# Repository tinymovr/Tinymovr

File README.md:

[Tinymovr is an affordable motor controller](https://tinymovr.com) with integrated encoder and CAN bus for precise control of 3-phase brushless motors (PMSMs). 

This repository holds the open source firmware, client library, hardware designs and documentation source.

> **Note**
>
> This is the latest stable version of the Tinymovr Firmware and Studio app. For the legacy 0.x.x version, check out the [legacy branch](https://github.com/tinymovr/Tinymovr/tree/attic/legacy).

## Getting Started

Please visit the [Quick Start Guide](https://tinymovr.readthedocs.io/en/latest/quickstart.html)

## Getting Help

[Full documentation is available at Readthedocs](https://tinymovr.readthedocs.io).

Please visit the [Discussions Page](https://github.com/tinymovr/Tinymovr/discussions) and the [Discord Server](https://discord.gg/vNvmpfthug) to ask any questions. If you are unable to find an answer to your question, you are welcome to [start a new discussion](https://github.com/tinymovr/Tinymovr/discussions/new/choose) or ask away at [our Discord server](https://discord.gg/vNvmpfthug).

If you would like to propose a feature or think you have found a bug, [open a new issue](https://github.com/tinymovr/Tinymovr/issues/new).

### Repository Structure

> **Note**: The `main` branch reflects the latest release. Development happens on [develop](https://github.com/tinymovr/Tinymovr/tree/develop).

The repository is organized as follows:

[firmware](./firmware/): Firmware for the PAC5527 MCU in Tinymovr

[studio](./studio/): Tinymovr Studio client software and library

[hardware](./hardware): Designs and drawings for related hardware

[docs](./docs): User documentation source (built with Sphinx)

See also: Developer documentation in root (ARCHITECTURE.md, CONTRIBUTING.md, etc.)

### Developer Documentation

For contributors and AI agents working with the codebase:

- **[ARCHITECTURE.md](ARCHITECTURE.md)** - System design and module organization
- **[CONTRIBUTING.md](CONTRIBUTING.md)** - Setup, workflow, and PR process
- **[SAFETY.md](SAFETY.md)** - Safety-critical constraints (read before modifying firmware)
- **[CLAUDE.md](CLAUDE.md)** - Navigation guide for AI agents

Additional technical documentation:
- [AVLOS_GUIDE.md](AVLOS_GUIDE.md) - Protocol modification workflow
- [CONVENTIONS.md](CONVENTIONS.md) - Code style and patterns
- [TESTING.md](TESTING.md) - Testing practices
- [STRUCTURE.md](STRUCTURE.md) - Directory organization
- [PAC5527_NOTES.md](PAC5527_NOTES.md) - MCU architecture

## Versioning

We use [SemVer](http://semver.org/) for versioning. For the versions available, see the [tags on this repository](https://github.com/tinymovr/tinymovr/tags). 

## Contributing

Pull requests are welcome. For major changes, please open an issue first to discuss what you would like to change.

**New contributors**: See [CONTRIBUTING.md](CONTRIBUTING.md) for setup instructions and workflow.

**AI agents**: See [CLAUDE.md](CLAUDE.md) for navigation and guidelines.

## License

[GPLv3](https://choosealicense.com/licenses/gpl-3.0/)

### External Links

[Tinymovr Website and Store](https://tinymovr.com)

[Blog](https://tinymovr.com/blogs/news)

[Discord server](https://discord.gg/vNvmpfthug)

[Project page on Hackaday](https://hackaday.io/project/168650-tinymovr-motor-controller)

[BLDC-Design-Help Repository](https://github.com/ThotAlion/BLDC-design-help), with lots of useful information and Tinymovr benchmarks

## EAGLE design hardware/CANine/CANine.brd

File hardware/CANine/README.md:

# CANine CAN Adapter

This is a USB Type-C <-> CAN Bus adapter. Itself it is an adaptation of the [CANable board](https://canable.io/). It features DF-13 connectors in addition to 2.54mm header, as well as a convenient DIP switch for setting CAN termination resistor and boot mode.

This design is released under the original CANable license.

This directory also includes an STL model for a 3D printable case for the adapter.

There is also an [alternative case design available](https://github.com/ThotAlion/BLDC-design-help/tree/main/STL/USBCANBox) by ThotAlion.

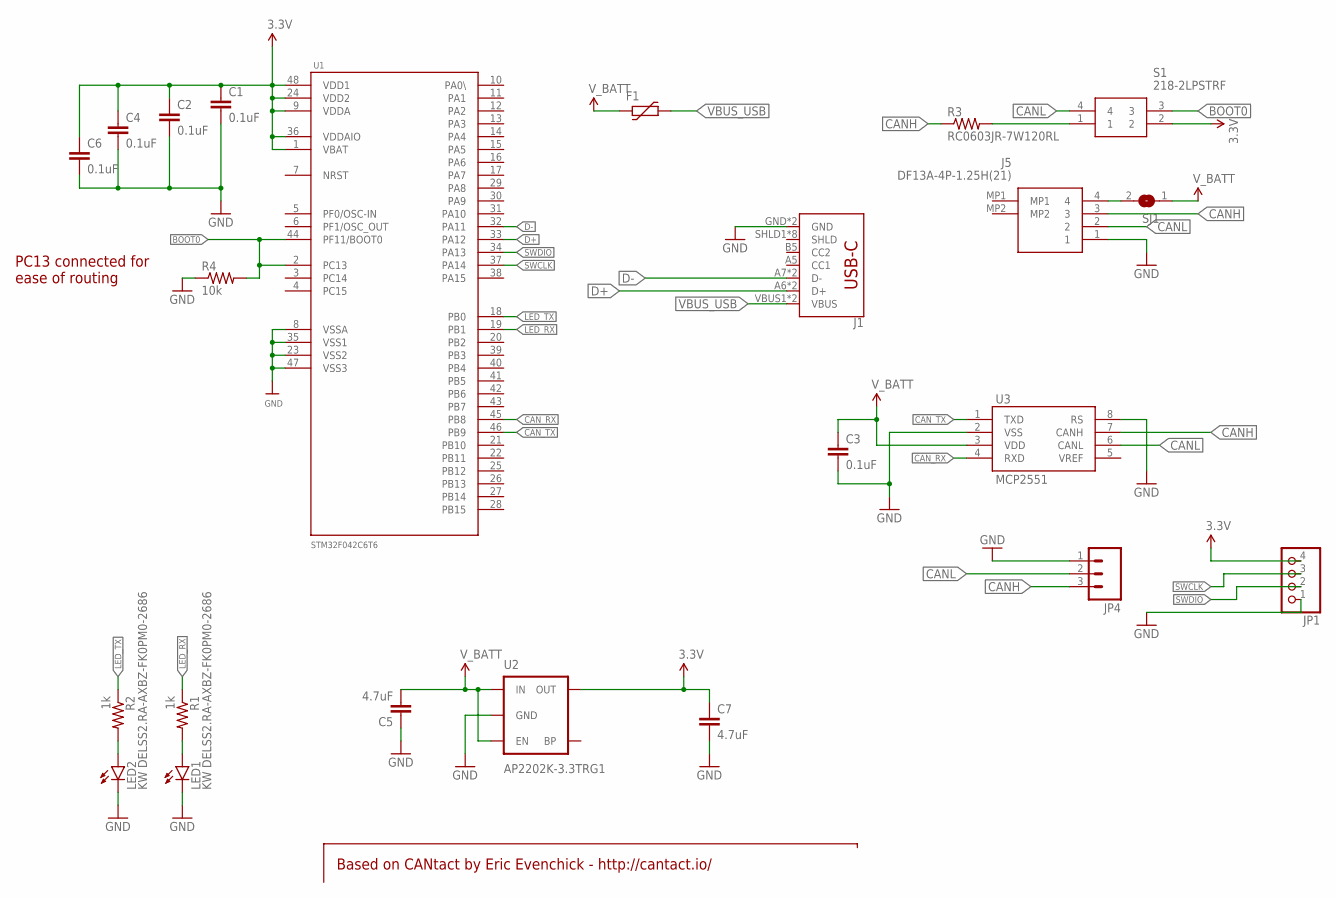
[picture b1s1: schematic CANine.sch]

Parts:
C1, C2, C3, C4, C6: 0.1uF; 0603-CAP
C5, C7: 4.7uF; 0603-CAP
F1: FUSE_PTC-0805; PTC0805
J1: SPARKFUN-CONNECTORS_USB_C16PIN; SPARKFUN-CONNECTORS_USB-C-16P
J5: DF13A-4P-1.25H(21); DF13A4P125H21
JP1: PINHD-1X04_2.54-S; 1X04-S
JP4: M03LOCK; 1X03_LOCK
LED1, LED2: KW DELSS2.RA-AXBZ-FK0PM0-2686; LED-0603
R1, R2: 1k; 0603-RES
R3: RC0603JR-7W120RL; 0603-RES
R4: 10k; 0603-RES
S1: 218-2LPSTRF; 2182LPSTRF
SJ1: SJ
U1: STM32F042C6T6; LQFP48
U2: AP2202K-3.3TRG1; SOT23-5
U3: MCP2551; SO08

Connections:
3.3V: C1.1, C2.1, C4.1, C6.1, C7.1, JP1.4, S1.2, U1.1 (VBAT), U1.9 (VDDA), U1.24 (VDD2), U1.36 (VDDAIO), U1.48 (VDD1), U2.5 (OUT)
BOOT0: R4.2, S1.3, U1.2 (PC13), U1.44 (PF11/BOOT0)
CANH: J5.3, JP4.3, R3.1, U3.7 (CANH)
CANL: J5.2, JP4.2, S1.4, U3.6 (CANL)
CAN_RX: U1.45 (PB8), U3.4 (RXD)
CAN_TX: U1.46 (PB9), U3.1 (TXD)
D+: J1.A6 (D+), J1.B6 (D+), U1.33 (PA12)
D-: J1.A7 (D-), J1.B7 (D-), U1.32 (PA11)
GND: C1.2, C2.2, C3.2, C4.2, C5.1, C6.2, C7.2, J1.GND, J1.GND2 (GND), J5.1, JP1.1, JP4.1, LED1.C, LED2.C, R4.1, U1.8 (VSSA), U1.23 (VSS2), U1.35 (VSS1), U1.47 (VSS3), U2.2 (GND), U3.2 (VSS), U3.8 (RS)
LED_RX: R1.1, U1.19 (PB1)
LED_TX: R2.1, U1.18 (PB0)
unnamed: LED2.A, R2.2
unnamed: R3.2, S1.1
unnamed: J5.4, SJ1.2
unnamed: LED1.A, R1.2
SWCLK: JP1.3, U1.37 (PA14)
SWDIO: JP1.2, U1.34 (PA13)
VBUS_USB: F1.2, J1.VBUS1 (VBUS), J1.VBUS2 (VBUS)
V_BATT: C3.1, C5.2, F1.1, SJ1.1, U2.1 (IN), U2.3 (EN), U3.3 (VDD)

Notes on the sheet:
Based on CANtact by Eric Evenchick - http://cantact.io/
PC13 connected for ease of routing

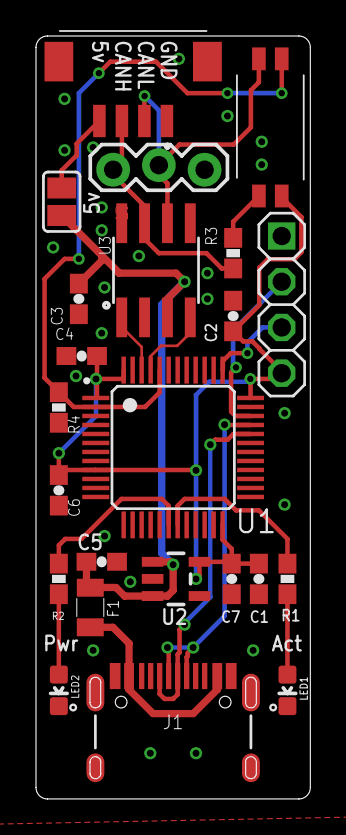
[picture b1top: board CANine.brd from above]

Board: 2 copper layers, 15.2 x 42.4 mm, 23 parts (0 on the bottom side), 19 nets.

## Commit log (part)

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2023-08-29 fix tests
2023-08-29 allow setting via string
2023-08-29 check if bin file specified and exists
2023-08-29 update firmware binaries
2023-08-29 fix test expected result
2023-08-29 separate widgets file
2023-08-29 update protocol with units
2023-08-29 add argument setting dialog
2023-08-31 add gate driver error status
2023-08-31 better formatting for bitmasks and enums
2023-08-31 use actual gate driver state
2023-08-31 update system in systick
2023-08-31 remove cycle reporting
2023-08-31 add adc offset calibration step
2023-08-31 ignore cp_stat error
2023-08-31 fix dynamic attribute getter to support enums and bitmasks
2023-08-31 formatting using black
2023-09-01 improve handling of comm timeouts
2023-09-02 move yaml files to own dir
2023-09-02 fix file locations
2023-09-02 enable working with multiple device specs
2023-09-02 only use the dfu util for fw upgrades
2023-09-02 update bootloader binaries
2023-09-05 rearrange delays
2023-09-05 increase speed in test
2023-09-05 refactor for readability
2023-09-05 increase bandwidth
2023-09-05 calculate size constant using bit count
2023-09-05 fix some offset related errors
2023-09-05 add legacy device specs for compatibility
2023-09-05 accumulate in single array
2023-09-05 outline all fw upgrade methods
2023-09-06 add studio develop instructions
2023-09-07 update dfu spec
2023-09-07 validate written data with checksum
2023-09-07 add recovery mode docs
2023-09-07 fix timing
2023-09-07 require avlos latest
2023-09-07 add testpypi script
2023-09-07 only install the latest available version
2023-09-07 remove script
2023-09-07 ignore built binaries
2023-09-07 add script to build all targets and variants
2023-09-07 fix manifest locations
2023-09-10 improve angle sensor docs
2023-09-13 fix uart commands
2023-09-13 rename files
2023-09-13 add gui commands
2023-09-13 fix title
2023-09-13 increase image size
2023-09-14 add configuring vscode section
2023-09-14 remove obsolete page
2023-09-14 ensure copied directory name
2023-09-18 compute offset at start
2023-09-18 ignore some errors
2023-09-18 discard erroneous computation
2023-09-18 remove deprecated setting
2023-09-18 remove unused variables
2023-09-19 rename function
2023-09-19 reset calibration
2023-09-21 disable driver errors returning spurious values
2023-09-21 rearrange functions
2023-09-21 remove unneeded attribute
2023-09-21 remove obsolete definition
2023-09-25 remove redundant
2023-09-25 add bus, channel and bitrate arguments to dfu util
2023-09-25 populate timing information
2023-09-27 also compare without flux braking and negative velocity
2023-09-27 add docs on custom device definitions
2023-10-09 all-around gui refactor and improvements
2023-10-09 add combo box callback
2023-10-09 fix function implementations
2023-10-09 formatting
2023-10-09 joggable text fields
2023-10-10 cleanup imports
2023-10-10 conditionally use joggable and plottable fields
2023-10-10 use optional fixed jog step
2023-10-10 remove unused attribute
2023-10-10 add class descriptions
2023-10-10 rename encoder to sensor
2023-10-10 initial spec refactor
2023-10-11 fix names disappearing
2023-10-11 only update fields not in focus (editing)
2023-10-11 use feed forward values for Vq, Vd
2023-10-28 rename to sensor
2023-10-28 refactor sensor
2023-10-29 refactor sensors for modularity
2023-10-29 fix quotations
2023-11-05 fix hall setup commands
2023-11-08 update sensor and observer structure
2023-11-09 revise sensor initialization
2023-11-10 add observer init
2023-11-10 minor refactor of sensor
2023-11-10 add daisy chaining guide
2023-11-10 add file required by readthedocs
2023-11-10 remove deprecated file
2023-11-12 rename sensor folder
2023-11-14 update spec
2023-11-16 update protocol
2023-11-16 format function name
2023-11-16 refactor sensor structure
2023-11-17 implement missing struct
2023-11-17 refactor sensor update loop
2023-12-06 rename variable
2023-12-06 cxx file associations
2023-12-06 update interface functions and summary
2023-12-09 implement some missing functions
2023-12-10 add compatibility flags
2023-12-10 align function name with standard
2023-12-10 align implementations with multi-sensor support
2023-12-22 various misnaming fixes
2023-12-23 builds
2023-12-29 add instrumentation timer for debug
2023-12-29 update includes
2023-12-29 introduce separate interface header and source file for access to sensors
2024-01-05 make offset and pole pair calibration sensor-generic
2024-01-05 add as5047 sensor
2024-01-06 change test limits
2024-01-06 allow adding custom spec files as cli parameters
2024-01-09 set initialize variable on init
2024-01-09 default values for the sensors struct
2024-01-10 Change sensor bits to 16
2024-01-10 consolidate sensor return types
2024-01-11 fix typo
2024-01-17 update docs
2024-01-22 fix integer fields not updating
2024-01-25 remove unused function
2024-01-28 refactor sensor initialization
2024-01-28 update requirements
2024-01-28 update theme selection
2024-01-28 remove unneeded requirements file
2024-01-28 specify requirements file
2024-01-29 fix indent
2024-01-29 remove pip
2024-01-31 fix size of returned firmware version
2024-02-02 add new bootloader definition
2024-02-03 fix erroneous functions pointers
2024-02-03 update SPI config
2024-02-03 add SPI mode mini cheat sheet
2024-02-03 add raw sensor angle reporting to device spec
2024-02-03 use pointer to each sensor pointer
2024-02-03 add fw_version bootloader endpoint
2024-02-04 add size of config object
2024-02-04 basic sensor working with m5
2024-02-06 fix sensor sector calculation
2024-02-06 set value of dropdown control
2024-02-07 introduce common sensor resolution
2024-02-07 add m5.2 board version
2024-02-07 fix underlines
2024-02-09 update limits
2024-02-12 introduce new transformations system to transform between different reference frames
2024-02-13 revise transforms
2024-02-15 inline functions
2024-02-15 use hash in arbitration id
2024-02-15 update bootloader
2024-02-15 support adding hash as parameter to functions
2024-02-15 revise dfu specs
2024-02-15 revise function detection
2024-02-15 fix returning trimmed string
2024-02-17 test iteratively
2024-02-17 use zero hash for initial communitacion
2024-02-25 use 1 to 1 transform for commutation
2024-02-25 remove unneeded onversion
2024-02-25 promote data types
2024-02-25 enforce minimum trip current value
2024-02-25 refactor calibration routines
2024-02-26 update variables
2024-02-27 update m5.2 pinouts
2024-02-28 remove spec
2024-02-28 update manifest
2024-02-28 add spec hash aliasing
2024-03-01 Make the scheduler state volatile
2024-03-02 integrate reference frames diagram
2024-03-13 add files
2024-03-13 fix accessor
2024-03-13 fix calibration frame issues
2024-03-13 init with default transforms
2024-03-13 fix eccentricity and frames calibration
2024-03-14 update transform library
2024-03-14 make struct extern
2024-03-15 add back dwt counter
2024-03-15 disable reading the peripheral at every cycle
2024-03-15 only prepare sensor once
2024-03-15 remove unused timer
2024-03-15 fix transforms
2024-03-17 make const
2024-03-17 fix velocity limiting issue
2024-03-17 rename can state struct
2024-03-18 update spec with new function signatures
2024-03-18 consolidate ref frame updates
2024-03-19 elaborate on sensor setup
2024-03-19 optimize some operations
2024-03-19 increase ssp rate for external sensor
2024-03-19 enable inverter before proceeding
2024-03-20 fix hall sector count
2024-03-20 report hall angle as full circle in ticks
2024-03-20 use sensor type getter
2024-03-20 update hall sensor config docs
2024-03-20 add get config implementations
2024-03-21 remove unused functions
2024-03-21 erase as many pages as needed
2024-03-26 use separate update params function
2024-03-26 init all members
2024-03-26 add initial amt22 support
2024-03-27 fix expired discord link
2024-04-01 update tests for new firmware
2024-04-01 refactor observer initialization
2024-04-01 update tests
2024-04-01 update figures
2024-04-01 update sensor docs
2024-04-01 add as5047 test
2024-04-01 fix reference
2024-04-01 elaborate on examples
2024-04-03 add more verbose pre- and post-build messages
2024-04-03 add note about commutation transform
2024-04-03 remove unused parameter
2024-04-04 toggle sending of heartbeat
2024-04-04 reset observer state
2024-04-04 fix scaling
2024-04-04 init sensors after uart and can
2024-04-04 explicit check
2024-04-04 reset observer state on change
2024-04-04 fix conversion
2024-04-04 rename vars
2024-04-04 Use proper checkboxes for boolean values
2024-04-05 add hall test
2024-04-06 change optimization level
2024-04-12 update only visible items
2024-04-13 add more external sensor tests
2024-04-13 add parity calculation for the amt22 sensor
2024-04-15 parametrize the ssp data size
2024-04-15 fix reading of AMT22
2024-04-16 add amt22 test
2024-04-17 track and use reference frame calibrations
2024-04-17 update as5047 tests
2024-04-19 change scheduler error to warning
2024-04-21 update protocol headers based on new spec
2024-04-21 add init_func for initialization using sensor pointer only
2024-04-21 add getter and setter for rate
2024-04-21 include spi rate as an init parameter
2024-04-21 config rates in blank objects
2024-04-21 add test for different baud rates
2024-04-26 add spec to manifest
2024-04-26 update simple test for compatibility with M5
2024-04-29 add app icon
2024-04-29 add adjustable splitter
2024-04-29 basic console implementation
2024-04-29 improve logging
2024-05-03 implement correct SPI delays according to amt22 datasheet
2024-05-03 compute checksum
2024-05-03 always set calibration current before calibration
2024-05-08 refactor bus discovery and management
2024-05-08 add busrouter api docs
2024-05-08 update sim (mock) test
2024-05-08 add python 3.12 to ci
2024-05-08 add generic sensor test mark
2024-05-08 refactor to pyproject.toml
2024-05-12 use alt string format in logging
2024-05-20 add logging message
2024-05-27 clear console
2024-05-27 Add configurable update rate
2024-05-27 add time window selection for plot
2024-05-29 improve pole pair calibration error reporting
2024-05-29 fix persistence of shared ram
2024-05-29 also set shared ram
2024-06-01 add power cycle dfu test
2024-06-05 initialize can and adc after loading config
2024-06-05 properly handle response error
2024-06-05 remove unneeded return
2024-06-06 add motor resistance and inductance limitations table
2024-06-06 fix erroneous return during transform derivation
2024-06-14 use wildcards
2024-06-24 add force flag for forcing device flashing
2024-06-26 reset can controller after a set interval has passed following a bus off event
2024-06-26 remove whitespace
2024-06-27 add test case
2024-06-27 update erratum
2024-07-01 Update expired Discord link
2024-07-06 validate data written to nvm
2024-07-06 add checksum validation
2024-07-07 fix saving and validating to nvm
2024-07-07 rename test
2024-07-14 relax some tests
2024-07-14 add pre-cl checks
2024-07-17 add abnormal calibration voltage check
2024-07-29 Refactor abnormal voltage check to be more robust
2024-08-19 add board options
2024-08-19 fix calibration sequence
2024-08-19 add hitl mini test group
2024-08-19 update external spi port for r53
2024-08-19 use filtered current for R measurement
2024-08-19 update test constants
2024-08-27 remove obsolete sensor information
2024-08-27 add remaining tinymovr connector figures
2024-08-27 complete unfinished section
2024-10-21 Hotfix: add FAQ to troubleshooting.rst
2024-11-25 add faq
2024-12-07 fix: replace tmx with tm1
2024-12-07 feat: Add default logger and optional parameter in bus_router initialization
2025-12-27 update quickstart with multiple node setup
2026-01-15 adapt tests to multiple hardware revisions
2026-01-16 move functions to ram
2026-01-17 add dual node id record at the start of the slot
2026-01-17 write to slot 0 if can id changes
2026-01-17 add dfu test with changing can id
2026-01-19 fix review issues
2026-01-30 upgrade uart protocol to full avlos spec
2026-01-30 remove dead code
2026-01-30 fix constants
2026-01-30 fix vulnerability
2026-01-31 add UART
2026-01-31 change char to uint8_t
2026-01-31 add integrating docs
2026-01-31 update uart protocol to conform to avlos
2026-01-31 remove unused code
2026-01-31 Apply suggestions from code review

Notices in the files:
parts and their libraries:
SparkFun-LED: Licensing: Creative Commons ShareAlike 4.0 International - https://creativecommons.org/licenses/by-sa/4.0
